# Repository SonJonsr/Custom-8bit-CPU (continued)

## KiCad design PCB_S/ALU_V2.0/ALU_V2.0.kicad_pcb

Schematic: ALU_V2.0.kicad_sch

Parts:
C1, C2, C3, C4, C5, C6, C7, C8: 22uF; C_0805; Voltage Rated 25V; Tolerance ±20%; Part CL21A226MAQNNNE; LCSC C45783
D1, D2, D3, D4, D5, D6, D7, D8, D9, D10, D11, D12, D13, D14, D15, D16, D17, D18, D19, D20, D21, D22, D23, D24, D25, D26, D27, D28, D29, D30, D31, D32, D33, D34, D35, D36: Red; D_0603; Part KT-0603R; LCSC C2286
H1, H2, H3, H4: MountingHole; MountingHole_3.2mm_M3
J1, J2, J3: Conn_02x08_Odd_Even; PinSocket_2x08_P2.54mm_Vertical
J4, J6: Conn_01x02_Pin; PinHeader_1x02_P2.54mm_Vertical
Q1, Q2, Q3, Q4, Q5, Q6, Q7, Q8, Q9, Q10, Q11, Q12, Q13, Q14, Q15, Q16, Q17, Q18, Q19, Q20, Q21, Q22, Q23, Q24, Q25, Q26, Q27, Q28, Q29, Q30, Q31, Q32, Q33, Q34, Q35, Q36, Q37, Q38, Q39, Q40, Q41, Q42, Q43, Q44, Q45, Q46, Q47, Q48, Q49, Q50, Q51, Q52, Q53, Q54, Q55, Q56, Q57, Q58, Q59, Q60, Q61, Q62, Q63, Q64, Q65, Q66, Q67, Q68, Q69, Q70, Q71, Q72, Q73, Q74, Q75, Q76, Q77, Q78, Q79, Q80, Q81, Q82, Q83, Q84, Q85, Q86, Q87, Q88, Q89, Q90, Q91, Q92, Q93, Q94, Q95, Q96, Q97, Q98, Q99, Q100, Q101, Q102, Q103, Q104, Q105, Q106, Q107, Q108, Q109, Q110, Q111, Q112, Q113, Q114, Q115, Q116, Q117, Q118, Q119, Q120, Q121, Q122, Q123, Q124, Q125, Q126, Q127, Q128, Q129, Q130, Q131, Q132, Q133, Q134, Q135, Q136, Q137, Q138, Q139, Q140, Q141, Q142, Q143, Q144, Q145, Q146, Q147, Q148, Q149, Q150, Q151, Q152, Q153, Q154, Q155, Q156, Q157, Q158, Q159, Q160, Q161, Q162, Q163, Q164, Q165, Q166, Q167, Q168, Q169, Q170, Q171, Q172, Q173, Q174, Q175, Q176, Q177, Q178, Q179, Q180, Q181, Q182, Q183, Q184, Q185, Q186, Q187, Q188, Q189, Q190, Q191, Q192, Q193, Q194, Q195, Q196, Q197, Q198, Q199, Q200, Q201, Q202, Q203, Q204, Q205, Q206, Q207, Q208, Q209, Q210, Q211, Q212, Q213, Q214, Q215, Q216, Q217, Q218, Q219, Q220, Q221, Q222, Q223, Q224, Q225, Q226, Q227, Q228, Q229, Q230, Q231, Q232, Q233, Q234, Q235, Q236, Q237, Q238, Q239, Q240, Q241, Q242, Q243, Q244, Q245, Q246, Q247, Q248, Q249, Q250, Q251, Q252, Q253, Q254, Q255, Q256, Q257, Q258, Q259, Q260, Q261, Q262, Q263, Q264, Q265, Q266, Q267, Q268, Q269, Q270, Q271, Q277, Q278, Q279, Q280, Q281, Q282, Q283, Q284, Q285, Q286, Q287, Q288, Q289, Q290: 2N7002; SOT-23; Part 2N7002; LCSC C8545
Q272, Q273, Q274, Q275, Q276, Q291, Q292, Q293, Q294, Q295, Q296, Q297, Q298, Q299, Q300, Q301, Q302, Q303, Q304, Q305, Q306, Q307, Q308, Q309, Q310, Q311, Q312, Q313, Q314, Q315, Q316, Q317, Q318, Q319, Q320: 2N7002; SOT-23
R1, R2, R3, R4, R5, R6, R7, R8, R9, R10, R11, R12, R13, R14, R15, R16, R17, R18, R19, R20, R21, R22, R23, R24, R25, R26, R27, R28, R29, R30, R31, R32, R33, R34, R35, R36, R37, R38, R39, R40, R41, R42, R43, R44, R45, R46, R47, R48, R49, R50, R51, R52, R53, R54, R55, R56, R57, R58, R59, R60, R61, R62, R63, R64, R65, R66, R67, R68, R69, R70, R71, R72, R73, R74, R75, R76, R77, R78, R79, R80, R81, R82, R83, R84, R85, R86, R87, R88, R89, R90, R91, R92, R93, R94, R95, R96, R97, R98, R99, R100, R101, R102, R103, R104, R105, R106, R107, R108, R109, R110, R111, R112, R113, R114, R115, R116, R117, R118, R119, R120, R121, R122, R123, R124, R125, R126, R127, R128, R129, R130, R131, R132, R133, R134, R135, R136, R137, R138, R139, R140, R141, R142, R143, R144, R145, R146, R147, R148, R149, R150, R151, R152, R153, R154, R155, R156, R157, R158, R159, R160, R161, R162, R163, R164, R165, R166, R167, R168, R169, R170, R171, R172, R173, R174, R175, R176, R177, R178, R179, R180, R181, R182, R183, R184, R185, R186, R187, R188, R189, R190, R191, R192, R193, R194, R195, R196, R197, R198, R199, R200, R201, R202, R203, R204: 10kΩ; R_0402; Overload Voltage (Max) 50V; Tolerance ±1%; Part 0402WGF1002TCE; LCSC C25744

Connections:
/C_in: J2.14, Q28.1 (G)
/C_out: J2.12, Q265.3 (D), Q320.1 (G), R125.2
/N: J1.15, J2.4, Q253.3 (D), Q279.1 (G), Q282.1 (G), Q290.1 (G), Q293.1 (G), Q310.1 (G), R120.2
/O: J2.10, Q286.3 (D), Q319.1 (G), R133.2
/U: J2.8, Q264.3 (D), Q318.1 (G), R124.2
/Z: J2.6, Q268.3 (D), Q269.3 (D), Q270.3 (D), Q271.3 (D), Q287.3 (D), Q288.3 (D), Q289.3 (D), Q290.3 (D), Q311.1 (G), R127.2
GND: C1.2, C2.2, C3.2, C4.2, C5.2, C6.2, C7.2, C8.2, D36.1, J1.4, J1.8, J1.12, J1.16, J2.2, J2.16, J4.2, J6.2, Q1.2 (S), Q2.2 (S), Q3.2 (S), Q4.2 (S), Q5.2 (S), Q6.2 (S), Q7.2 (S), Q8.2 (S), Q9.2 (S), Q10.2 (S), Q11.2 (S), Q12.2 (S), Q13.2 (S), Q14.2 (S), Q15.2 (S), Q16.2 (S), Q17.2 (S), Q18.2 (S), Q19.2 (S), Q20.2 (S), Q21.2 (S), Q22.2 (S), Q23.2 (S), Q24.2 (S), Q26.2 (S), Q28.2 (S), Q31.2 (S), Q33.2 (S), Q35.2 (S), Q38.2 (S), Q41.2 (S), Q43.2 (S), Q46.2 (S), Q48.2 (S), Q50.2 (S), Q53.2 (S), Q56.2 (S), Q58.2 (S), Q61.2 (S), Q63.2 (S), Q65.2 (S), Q68.2 (S), Q71.2 (S), Q73.2 (S), Q76.2 (S), Q78.2 (S), Q80.2 (S), Q83.2 (S), Q86.2 (S), Q88.2 (S), Q91.2 (S), Q93.2 (S), Q95.2 (S), Q98.2 (S), Q101.2 (S), Q103.2 (S), Q106.2 (S), Q108.2 (S), Q110.2 (S), Q113.2 (S), Q116.2 (S), Q118.2 (S), Q121.2 (S), Q123.2 (S), Q125.2 (S), Q128.2 (S), Q131.2 (S), Q133.2 (S), Q136.2 (S), Q138.2 (S), Q140.2 (S), Q143.2 (S), Q146.2 (S), Q155.2 (S), Q156.2 (S), Q157.2 (S), Q158.2 (S), Q159.2 (S), Q160.2 (S), Q161.2 (S), Q162.2 (S), Q164.2 (S), Q166.2 (S), Q168.2 (S), Q170.2 (S), Q172.2 (S), Q174.2 (S), Q176.2 (S), Q178.2 (S), Q180.2 (S), Q182.2 (S), Q184.2 (S), Q186.2 (S), Q188.2 (S), Q190.2 (S), Q192.2 (S), Q194.2 (S), Q196.2 (S), Q198.2 (S), Q200.2 (S), Q202.2 (S), Q204.2 (S), Q206.2 (S), Q208.2 (S), Q210.2 (S), Q212.2 (S), Q214.2 (S), Q216.2 (S), Q218.2 (S), Q220.2 (S), Q222.2 (S), Q224.2 (S), Q226.2 (S), Q228.2 (S), Q230.2 (S), Q232.2 (S), Q234.2 (S), Q236.2 (S), Q238.2 (S), Q240.2 (S), Q242.2 (S), Q244.2 (S), Q246.2 (S), Q248.2 (S), Q250.2 (S), Q252.2 (S), Q254.2 (S), Q255.2 (S), Q256.2 (S), Q257.2 (S), Q258.2 (S), Q259.2 (S), Q260.2 (S), Q261.2 (S), Q263.2 (S), Q264.2 (S), Q265.2 (S), Q267.2 (S), Q268.2 (S), Q269.2 (S), Q270.2 (S), Q271.2 (S), Q272.2 (S), Q273.2 (S), Q274.2 (S), Q275.2 (S), Q276.2 (S), Q277.2 (S), Q278.2 (S), Q281.2 (S), Q282.2 (S), Q285.2 (S), Q286.2 (S), Q287.2 (S), Q288.2 (S), Q289.2 (S), Q290.2 (S), Q291.2 (S), Q292.2 (S), Q293.2 (S), Q294.2 (S), Q295.2 (S), Q296.2 (S), Q297.2 (S), Q298.2 (S), Q299.2 (S), Q300.2 (S), Q301.2 (S), Q302.2 (S), Q303.2 (S), Q304.2 (S), Q305.2 (S), Q306.2 (S), Q307.2 (S), Q308.2 (S), Q309.2 (S), Q310.2 (S), Q311.2 (S), Q312.2 (S), Q313.2 (S), Q314.2 (S), Q315.2 (S), Q316.2 (S), Q317.2 (S), Q318.2 (S), Q319.2 (S), Q320.2 (S)
unnamed: D1.2, R128.2, R134.2
unnamed: D2.2, R135.2, R136.2
unnamed: D3.2, R137.2, R138.2
unnamed: D4.2, R139.2, R140.2
unnamed: D5.2, R175.2, R176.2
unnamed: D6.2, R177.2, R178.2
unnamed: D7.2, R179.2, R180.2
unnamed: D8.2, R181.2, R182.2
unnamed: D9.2, R141.2, R142.2
unnamed: D10.2, R143.2, R144.2
unnamed: D11.2, R145.2, R146.2
unnamed: D12.2, R147.2, R148.2
unnamed: D13.2, R189.2, R190.2
unnamed: D14.2, R191.2, R192.2
unnamed: D15.2, R193.2, R194.2
unnamed: D16.2, R195.2, R196.2
unnamed: D17.2, R149.2, R150.2
unnamed: D18.2, R151.2, R152.2
unnamed: D19.2, R153.2, R154.2
unnamed: D20.2, R155.2, R156.2
unnamed: D21.2, R197.2, R198.2
unnamed: D22.2, R199.2, R200.2
unnamed: D23.2, R201.2, R202.2
unnamed: D24.2, R203.2, R204.2
unnamed: D25.2, R173.2, R174.2
unnamed: D26.2, R171.2, R172.2
unnamed: D27.2, R159.2, R160.2
unnamed: D28.2, R161.2, R162.2
unnamed: D29.2, R163.2, R164.2
unnamed: D30.2, R183.2, R184.2
unnamed: D31.2, R185.2, R186.2
unnamed: D32.2, R187.2, R188.2
unnamed: D33.2, R167.2, R170.2
unnamed: D34.2, R165.2, R166.2
unnamed: D35.2, R157.2, R158.2
unnamed: D36.2, R168.2, R169.2
unnamed: J1.1, Q239.3 (D), Q268.1 (G), Q273.1 (G), R113.2
unnamed: J1.3, Q241.3 (D), Q269.1 (G), Q272.1 (G), R114.2
unnamed: J1.5, Q243.3 (D), Q270.1 (G), Q274.1 (G), R115.2
unnamed: J1.7, Q245.3 (D), Q271.1 (G), Q275.1 (G), R116.2
unnamed: J1.9, Q247.3 (D), Q276.1 (G), Q287.1 (G), R117.2
unnamed: J1.11, Q249.3 (D), Q288.1 (G), Q291.1 (G), R118.2
unnamed: J1.13, Q251.3 (D), Q289.1 (G), Q292.1 (G), R119.2
unnamed: J2.3, Q210.1 (G), Q212.1 (G), Q214.1 (G), Q216.1 (G), Q218.1 (G), Q220.1 (G), Q222.1 (G), Q224.1 (G), Q260.1 (G), Q267.1 (G), Q317.1 (G)
unnamed: J2.5, Q180.1 (G), Q184.1 (G), Q188.1 (G), Q192.1 (G), Q196.1 (G), Q200.1 (G), Q204.1 (G), Q208.1 (G), Q259.1 (G), Q316.1 (G)
unnamed: J2.7, Q178.1 (G), Q182.1 (G), Q186.1 (G), Q190.1 (G), Q194.1 (G), Q198.1 (G), Q202.1 (G), Q206.1 (G), Q258.1 (G), Q315.1 (G)
unnamed: J2.9, Q226.1 (G), Q228.1 (G), Q230.1 (G), Q232.1 (G), Q234.1 (G), Q236.1 (G), Q238.1 (G), Q257.1 (G), Q263.1 (G), Q314.1 (G)
unnamed: J2.11, Q146.1 (G), Q164.1 (G), Q166.1 (G), Q168.1 (G), Q170.1 (G), Q172.1 (G), Q174.1 (G), Q176.1 (G), Q256.1 (G), Q313.1 (G)
unnamed: J2.13, Q155.1 (G), Q156.1 (G), Q157.1 (G), Q158.1 (G), Q159.1 (G), Q160.1 (G), Q161.1 (G), Q162.1 (G), Q255.1 (G), Q312.1 (G)
unnamed: J3.1, Q2.1 (G), Q34.1 (G), Q36.1 (G), Q294.1 (G)
unnamed: J3.2, Q1.1 (G), Q33.1 (G), Q262.1 (G), Q302.1 (G)
unnamed: J3.3, Q5.1 (G), Q49.1 (G), Q51.1 (G), Q295.1 (G)
unnamed: J3.4, Q4.1 (G), Q48.1 (G), Q225.1 (G), Q303.1 (G)
unnamed: J3.5, Q8.1 (G), Q64.1 (G), Q66.1 (G), Q296.1 (G)
unnamed: J3.6, Q7.1 (G), Q63.1 (G), Q227.1 (G), Q304.1 (G)
unnamed: J3.7, Q11.1 (G), Q79.1 (G), Q81.1 (G), Q297.1 (G)
unnamed: J3.8, Q10.1 (G), Q78.1 (G), Q229.1 (G), Q305.1 (G)
unnamed: J3.9, Q14.1 (G), Q94.1 (G), Q96.1 (G), Q298.1 (G)
unnamed: J3.10, Q13.1 (G), Q93.1 (G), Q231.1 (G), Q306.1 (G)
unnamed: J3.11, Q17.1 (G), Q109.1 (G), Q111.1 (G), Q299.1 (G)
unnamed: J3.12, Q16.1 (G), Q108.1 (G), Q233.1 (G), Q307.1 (G)
unnamed: J3.13, Q20.1 (G), Q124.1 (G), Q126.1 (G), Q300.1 (G)
unnamed: J3.14, Q19.1 (G), Q123.1 (G), Q235.1 (G), Q308.1 (G)
unnamed: J3.15, Q23.1 (G), Q139.1 (G), Q141.1 (G), Q278.1 (G), Q284.1 (G), Q301.1 (G)
unnamed: J3.16, Q22.1 (G), Q138.1 (G), Q237.1 (G), Q277.1 (G), Q285.1 (G), Q309.1 (G)
unnamed: Q1.3 (D), Q2.3 (D), Q3.1 (G), R1.2
unnamed: Q4.3 (D), Q5.3 (D), Q6.1 (G), R3.2
unnamed: Q7.3 (D), Q8.3 (D), Q9.1 (G), R5.2
unnamed: Q10.3 (D), Q11.3 (D), Q12.1 (G), R7.2
unnamed: Q12.3 (D), Q151.1 (G), R8.2
unnamed: Q13.3 (D), Q14.3 (D), Q15.1 (G), R9.2
unnamed: Q15.3 (D), Q150.1 (G), R10.2
unnamed: Q16.3 (D), Q17.3 (D), Q18.1 (G), R11.2
unnamed: Q19.3 (D), Q20.3 (D), Q21.1 (G), R13.2
unnamed: Q22.3 (D), Q23.3 (D), Q24.1 (G), R15.2
unnamed: Q25.3 (D), Q26.1 (G), R17.2
unnamed: Q25.1 (G), Q30.1 (G), Q34.3 (D), Q35.1 (G), R23.2
unnamed: Q26.3 (D), Q27.2 (S)
unnamed: Q27.1 (G), Q36.3 (D), R25.2
unnamed: Q28.3 (D), Q29.2 (S), Q37.2 (S)
unnamed: Q29.3 (D), Q31.1 (G), R19.2
unnamed: Q29.1 (G), Q37.3 (D), Q38.1 (G), R26.2
unnamed: Q30.3 (D), Q43.1 (G), R20.2
unnamed: Q30.2 (S), Q38.3 (D), Q39.2 (S)
unnamed: Q31.3 (D), Q32.2 (S)
unnamed: Q32.1 (G), Q39.3 (D), R27.2
unnamed: Q40.3 (D), Q41.1 (G), R28.2
unnamed: Q40.1 (G), Q45.1 (G), Q49.3 (D), Q50.1 (G), R34.2
unnamed: Q41.3 (D), Q42.2 (S)
unnamed: Q42.1 (G), Q51.3 (D), R36.2
unnamed: Q43.3 (D), Q44.2 (S), Q52.2 (S)
unnamed: Q44.3 (D), Q46.1 (G), R30.2
unnamed: Q44.1 (G), Q52.3 (D), Q53.1 (G), R37.2
unnamed: Q45.3 (D), Q58.1 (G), R31.2
unnamed: Q45.2 (S), Q53.3 (D), Q54.2 (S)
unnamed: Q46.3 (D), Q47.2 (S)
unnamed: Q47.1 (G), Q54.3 (D), R38.2
unnamed: Q55.3 (D), Q56.1 (G), R39.2
unnamed: Q55.1 (G), Q60.1 (G), Q64.3 (D), Q65.1 (G), R45.2
unnamed: Q56.3 (D), Q57.2 (S)
unnamed: Q57.1 (G), Q66.3 (D), R47.2
unnamed: Q58.3 (D), Q59.2 (S), Q67.2 (S)
unnamed: Q59.3 (D), Q61.1 (G), R41.2
unnamed: Q59.1 (G), Q67.3 (D), Q68.1 (G), R48.2
unnamed: Q60.3 (D), Q73.1 (G), R42.2
unnamed: Q60.2 (S), Q68.3 (D), Q69.2 (S)
unnamed: Q61.3 (D), Q62.2 (S)
unnamed: Q62.1 (G), Q69.3 (D), R49.2
unnamed: Q70.3 (D), Q71.1 (G), R50.2
unnamed: Q70.1 (G), Q75.1 (G), Q79.3 (D), Q80.1 (G), R56.2
unnamed: Q71.3 (D), Q72.2 (S)
unnamed: Q72.1 (G), Q81.3 (D), R58.2
unnamed: Q73.3 (D), Q74.2 (S), Q82.2 (S)
unnamed: Q74.3 (D), Q76.1 (G), R52.2
unnamed: Q74.1 (G), Q82.3 (D), Q83.1 (G), R59.2
unnamed: Q75.3 (D), Q88.1 (G), R53.2
unnamed: Q75.2 (S), Q83.3 (D), Q84.2 (S)
unnamed: Q76.3 (D), Q77.2 (S)
unnamed: Q77.1 (G), Q84.3 (D), R60.2
unnamed: Q85.3 (D), Q86.1 (G), R61.2
unnamed: Q85.1 (G), Q90.1 (G), Q94.3 (D), Q95.1 (G), R67.2
unnamed: Q86.3 (D), Q87.2 (S)
unnamed: Q87.1 (G), Q96.3 (D), R69.2
unnamed: Q88.3 (D), Q89.2 (S), Q97.2 (S)
unnamed: Q89.3 (D), Q91.1 (G), R63.2
unnamed: Q89.1 (G), Q97.3 (D), Q98.1 (G), R70.2
unnamed: Q90.2 (S), Q98.3 (D), Q99.2 (S)
unnamed: Q91.3 (D), Q92.2 (S)
unnamed: Q92.1 (G), Q99.3 (D), R71.2
unnamed: Q100.3 (D), Q101.1 (G), R72.2
unnamed: Q100.1 (G), Q105.1 (G), Q109.3 (D), Q110.1 (G), R78.2
unnamed: Q100.2 (S), Q108.3 (D), Q109.2 (S), Q197.1 (G), R77.2
unnamed: Q101.3 (D), Q102.2 (S)
unnamed: Q102.3 (D), Q112.1 (G), Q114.1 (G), Q199.1 (G), R73.2
unnamed: Q102.1 (G), Q111.3 (D), R80.2
unnamed: Q103.3 (D), Q104.2 (S), Q112.2 (S)
unnamed: Q90.3 (D), Q103.1 (G), R64.2
unnamed: Q104.3 (D), Q106.1 (G), R74.2
unnamed: Q104.1 (G), Q112.3 (D), Q113.1 (G), R81.2
unnamed: Q105.3 (D), Q118.1 (G), R75.2
unnamed: Q105.2 (S), Q113.3 (D), Q114.2 (S)
unnamed: Q106.3 (D), Q107.2 (S)
unnamed: Q107.3 (D), Q219.1 (G), R76.2
unnamed: Q107.1 (G), Q114.3 (D), R82.2
unnamed: Q110.3 (D), Q111.2 (S), Q171.1 (G), R79.2
unnamed: Q115.3 (D), Q116.1 (G), R83.2
unnamed: Q115.1 (G), Q120.1 (G), Q124.3 (D), Q125.1 (G), R89.2
unnamed: Q115.2 (S), Q123.3 (D), Q124.2 (S), Q201.1 (G), R88.2
unnamed: Q116.3 (D), Q117.2 (S)
unnamed: Q117.3 (D), Q127.1 (G), Q129.1 (G), Q203.1 (G), R84.2
unnamed: Q117.1 (G), Q126.3 (D), R91.2
unnamed: Q118.3 (D), Q119.2 (S), Q127.2 (S)
unnamed: Q119.3 (D), Q121.1 (G), R85.2
unnamed: Q119.1 (G), Q127.3 (D), Q128.1 (G), R92.2
unnamed: Q120.3 (D), Q133.1 (G), R86.2
unnamed: Q120.2 (S), Q128.3 (D), Q129.2 (S)
unnamed: Q121.3 (D), Q122.2 (S)
unnamed: Q122.3 (D), Q221.1 (G), R87.2
unnamed: Q122.1 (G), Q129.3 (D), R93.2
unnamed: Q125.3 (D), Q126.2 (S), Q173.1 (G), R90.2
unnamed: Q130.3 (D), Q131.1 (G), R94.2
unnamed: Q130.1 (G), Q135.1 (G), Q139.3 (D), Q140.1 (G), R100.2
unnamed: Q130.2 (S), Q138.3 (D), Q139.2 (S), Q205.1 (G), R99.2
unnamed: Q131.3 (D), Q132.2 (S)
unnamed: Q132.3 (D), Q142.1 (G), Q144.1 (G), Q207.1 (G), R95.2
unnamed: Q132.1 (G), Q141.3 (D), R102.2
unnamed: Q133.3 (D), Q134.2 (S), Q142.2 (S)
unnamed: Q134.3 (D), Q136.1 (G), R96.2
unnamed: Q134.1 (G), Q142.3 (D), Q143.1 (G), R103.2
unnamed: Q135.3 (D), Q266.1 (G), R97.2
unnamed: Q135.2 (S), Q143.3 (D), Q144.2 (S)
unnamed: Q136.3 (D), Q137.2 (S)
unnamed: Q137.3 (D), Q223.1 (G), R98.2
unnamed: Q137.1 (G), Q144.3 (D), R104.2
unnamed: Q140.3 (D), Q141.2 (S), Q175.1 (G), R101.2
unnamed: Q145.3 (D), Q154.3 (D), Q177.3 (D), Q179.3 (D), Q209.3 (D), Q225.3 (D), Q239.1 (G), R105.2
unnamed: Q35.3 (D), Q36.2 (S), Q145.1 (G), R24.2
unnamed: Q145.2 (S), Q146.3 (D)
unnamed: Q147.3 (D), Q175.3 (D), Q205.3 (D), Q207.3 (D), Q223.3 (D), Q253.1 (G), R112.2
unnamed: Q24.3 (D), Q147.1 (G), R16.2
unnamed: Q147.2 (S), Q162.3 (D)
unnamed: Q148.3 (D), Q173.3 (D), Q201.3 (D), Q203.3 (D), Q221.3 (D), Q237.3 (D), Q251.1 (G), R111.2
unnamed: Q21.3 (D), Q148.1 (G), R14.2
unnamed: Q148.2 (S), Q161.3 (D)
unnamed: Q149.3 (D), Q171.3 (D), Q197.3 (D), Q199.3 (D), Q219.3 (D), Q235.3 (D), Q249.1 (G), R110.2
unnamed: Q18.3 (D), Q149.1 (G), R12.2
unnamed: Q149.2 (S), Q160.3 (D)
unnamed: Q150.3 (D), Q169.3 (D), Q193.3 (D), Q195.3 (D), Q217.3 (D), Q233.3 (D), Q247.1 (G), R109.2
unnamed: Q150.2 (S), Q159.3 (D)
unnamed: Q151.3 (D), Q167.3 (D), Q189.3 (D), Q191.3 (D), Q215.3 (D), Q231.3 (D), Q245.1 (G), R108.2
unnamed: Q151.2 (S), Q158.3 (D)
unnamed: Q152.3 (D), Q165.3 (D), Q185.3 (D), Q187.3 (D), Q213.3 (D), Q229.3 (D), Q243.1 (G), R107.2
unnamed: Q9.3 (D), Q152.1 (G), R6.2
unnamed: Q152.2 (S), Q157.3 (D)
unnamed: Q153.3 (D), Q163.3 (D), Q181.3 (D), Q183.3 (D), Q211.3 (D), Q227.3 (D), Q241.1 (G), R106.2
unnamed: Q6.3 (D), Q153.1 (G), R4.2
unnamed: Q153.2 (S), Q156.3 (D)
unnamed: Q3.3 (D), Q154.1 (G), R2.2
unnamed: Q154.2 (S), Q155.3 (D)
unnamed: Q50.3 (D), Q51.2 (S), Q163.1 (G), R35.2
unnamed: Q163.2 (S), Q164.3 (D)
unnamed: Q65.3 (D), Q66.2 (S), Q165.1 (G), R46.2
unnamed: Q165.2 (S), Q166.3 (D)
unnamed: Q80.3 (D), Q81.2 (S), Q167.1 (G), R57.2
unnamed: Q167.2 (S), Q168.3 (D)
unnamed: Q95.3 (D), Q96.2 (S), Q169.1 (G), R68.2
unnamed: Q169.2 (S), Q170.3 (D)
unnamed: Q171.2 (S), Q172.3 (D)
unnamed: Q173.2 (S), Q174.3 (D)
unnamed: Q175.2 (S), Q176.3 (D)
unnamed: Q25.2 (S), Q33.3 (D), Q34.2 (S), Q177.1 (G), R22.2
unnamed: Q177.2 (S), Q178.3 (D)
unnamed: Q27.3 (D), Q37.1 (G), Q39.1 (G), Q179.1 (G), R18.2
unnamed: Q179.2 (S), Q180.3 (D)
unnamed: Q40.2 (S), Q48.3 (D), Q49.2 (S), Q181.1 (G), R33.2
unnamed: Q181.2 (S), Q182.3 (D)
unnamed: Q42.3 (D), Q52.1 (G), Q54.1 (G), Q183.1 (G), R29.2
unnamed: Q183.2 (S), Q184.3 (D)
unnamed: Q55.2 (S), Q63.3 (D), Q64.2 (S), Q185.1 (G), R44.2
unnamed: Q185.2 (S), Q186.3 (D)
unnamed: Q57.3 (D), Q67.1 (G), Q69.1 (G), Q187.1 (G), R40.2
unnamed: Q187.2 (S), Q188.3 (D)
unnamed: Q70.2 (S), Q78.3 (D), Q79.2 (S), Q189.1 (G), R55.2
unnamed: Q189.2 (S), Q190.3 (D)
unnamed: Q72.3 (D), Q82.1 (G), Q84.1 (G), Q191.1 (G), R51.2
unnamed: Q191.2 (S), Q192.3 (D)
unnamed: Q85.2 (S), Q93.3 (D), Q94.2 (S), Q193.1 (G), R66.2
unnamed: Q193.2 (S), Q194.3 (D)
unnamed: Q87.3 (D), Q97.1 (G), Q99.1 (G), Q195.1 (G), R62.2
unnamed: Q195.2 (S), Q196.3 (D)
unnamed: Q197.2 (S), Q198.3 (D)
unnamed: Q199.2 (S), Q200.3 (D)
unnamed: Q201.2 (S), Q202.3 (D)
unnamed: Q203.2 (S), Q204.3 (D)
unnamed: Q205.2 (S), Q206.3 (D)
unnamed: Q207.2 (S), Q208.3 (D)
unnamed: Q32.3 (D), Q209.1 (G), R21.2
unnamed: Q209.2 (S), Q210.3 (D)
unnamed: Q47.3 (D), Q211.1 (G), R32.2
unnamed: Q211.2 (S), Q212.3 (D)
unnamed: Q62.3 (D), Q213.1 (G), R43.2
unnamed: Q213.2 (S), Q214.3 (D)
unnamed: Q77.3 (D), Q215.1 (G), R54.2
unnamed: Q215.2 (S), Q216.3 (D)
unnamed: Q92.3 (D), Q217.1 (G), R65.2
unnamed: Q217.2 (S), Q218.3 (D)
unnamed: Q219.2 (S), Q220.3 (D)
unnamed: Q221.2 (S), Q222.3 (D)
unnamed: Q223.2 (S), Q224.3 (D)
unnamed: Q225.2 (S), Q226.3 (D)
unnamed: Q227.2 (S), Q228.3 (D)
unnamed: Q229.2 (S), Q230.3 (D)
unnamed: Q231.2 (S), Q232.3 (D)
unnamed: Q233.2 (S), Q234.3 (D)
unnamed: Q235.2 (S), Q236.3 (D)
unnamed: Q237.2 (S), Q238.3 (D)
unnamed: Q239.2 (S), Q240.3 (D)
unnamed: Q240.1 (G), Q242.1 (G), Q244.1 (G), Q246.1 (G), Q248.1 (G), Q250.1 (G), Q252.1 (G), Q254.1 (G), Q261.3 (D), R121.2
unnamed: Q241.2 (S), Q242.3 (D)
unnamed: Q243.2 (S), Q244.3 (D)
unnamed: Q245.2 (S), Q246.3 (D)
unnamed: Q247.2 (S), Q248.3 (D)
unnamed: Q249.2 (S), Q250.3 (D)
unnamed: Q251.2 (S), Q252.3 (D)
unnamed: Q253.2 (S), Q254.3 (D)
unnamed: Q255.3 (D), Q256.3 (D), Q257.3 (D), Q258.3 (D), Q259.3 (D), Q260.3 (D), Q261.1 (G), R122.2
unnamed: Q262.3 (D), Q264.1 (G), R123.2
unnamed: Q262.2 (S), Q263.3 (D)
unnamed: Q265.1 (G), Q266.3 (D), R126.2
unnamed: Q266.2 (S), Q267.3 (D)
unnamed: D2.1, Q272.3 (D)
unnamed: D1.1, Q273.3 (D)
unnamed: D3.1, Q274.3 (D)
unnamed: D4.1, Q275.3 (D)
unnamed: D5.1, Q276.3 (D)
unnamed: Q277.3 (D), Q281.1 (G), R129.2
unnamed: Q278.3 (D), Q280.1 (G), R130.2
unnamed: Q279.3 (D), Q283.3 (D), Q286.1 (G), R132.2
unnamed: Q279.2 (S), Q280.3 (D)
unnamed: Q280.2 (S), Q281.3 (D)
unnamed: Q282.3 (D), Q283.1 (G), R131.2
unnamed: Q283.2 (S), Q284.3 (D)
unnamed: Q284.2 (S), Q285.3 (D)
unnamed: D6.1, Q291.3 (D)
unnamed: D7.1, Q292.3 (D)
unnamed: D8.1, Q293.3 (D)
unnamed: D9.1, Q294.3 (D)
unnamed: D10.1, Q295.3 (D)
unnamed: D11.1, Q296.3 (D)
unnamed: D12.1, Q297.3 (D)
unnamed: D13.1, Q298.3 (D)
unnamed: D14.1, Q299.3 (D)
unnamed: D15.1, Q300.3 (D)
unnamed: D16.1, Q301.3 (D)
unnamed: D17.1, Q302.3 (D)
unnamed: D18.1, Q303.3 (D)
unnamed: D19.1, Q304.3 (D)
unnamed: D20.1, Q305.3 (D)
unnamed: D21.1, Q306.3 (D)
unnamed: D22.1, Q307.3 (D)
unnamed: D23.1, Q308.3 (D)
unnamed: D24.1, Q309.3 (D)
unnamed: D25.1, Q310.3 (D)
unnamed: D26.1, Q311.3 (D)
unnamed: D27.1, Q312.3 (D)
unnamed: D28.1, Q313.3 (D)
unnamed: D29.1, Q314.3 (D)
unnamed: D30.1, Q315.3 (D)
unnamed: D31.1, Q316.3 (D)
unnamed: D32.1, Q317.3 (D)
unnamed: D33.1, Q318.3 (D)
unnamed: D34.1, Q319.3 (D)
unnamed: D35.1, Q320.3 (D)
VCC: C1.1, C2.1, C3.1, C4.1, C5.1, C6.1, C7.1, C8.1, J1.2, J1.6, J1.10, J1.14, J2.1, J2.15, J4.1, J6.1, R1.1, R2.1, R3.1, R4.1, R5.1, R6.1, R7.1, R8.1, R9.1, R10.1, R11.1, R12.1, R13.1, R14.1, R15.1, R16.1, R17.1, R18.1, R19.1, R20.1, R21.1, R22.1, R23.1, R24.1, R25.1, R26.1, R27.1, R28.1, R29.1, R30.1, R31.1, R32.1, R33.1, R34.1, R35.1, R36.1, R37.1, R38.1, R39.1, R40.1, R41.1, R42.1, R43.1, R44.1, R45.1, R46.1, R47.1, R48.1, R49.1, R50.1, R51.1, R52.1, R53.1, R54.1, R55.1, R56.1, R57.1, R58.1, R59.1, R60.1, R61.1, R62.1, R63.1, R64.1, R65.1, R66.1, R67.1, R68.1, R69.1, R70.1, R71.1, R72.1, R73.1, R74.1, R75.1, R76.1, R77.1, R78.1, R79.1, R80.1, R81.1, R82.1, R83.1, R84.1, R85.1, R86.1, R87.1, R88.1, R89.1, R90.1, R91.1, R92.1, R93.1, R94.1, R95.1, R96.1, R97.1, R98.1, R99.1, R100.1, R101.1, R102.1, R103.1, R104.1, R105.1, R106.1, R107.1, R108.1, R109.1, R110.1, R111.1, R112.1, R113.1, R114.1, R115.1, R116.1, R117.1, R118.1, R119.1, R120.1, R121.1, R122.1, R123.1, R124.1, R125.1, R126.1, R127.1, R128.1, R129.1, R130.1, R131.1, R132.1, R133.1, R134.1, R135.1, R136.1, R137.1, R138.1, R139.1, R140.1, R141.1, R142.1, R143.1, R144.1, R145.1, R146.1, R147.1, R148.1, R149.1, R150.1, R151.1, R152.1, R153.1, R154.1, R155.1, R156.1, R157.1, R158.1, R159.1, R160.1, R161.1, R162.1, R163.1, R164.1, R165.1, R166.1, R167.1, R168.1, R169.1, R170.1, R171.1, R172.1, R173.1, R174.1, R175.1, R176.1, R177.1, R178.1, R179.1, R180.1, R181.1, R182.1, R183.1, R184.1, R185.1, R186.1, R187.1, R188.1, R189.1, R190.1, R191.1, R192.1, R193.1, R194.1, R195.1, R196.1, R197.1, R198.1, R199.1, R200.1, R201.1, R202.1, R203.1, R204.1

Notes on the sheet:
Result
Dont need these resistors
Carry Inn
Pin 1 is Most Significant Bit
ADD
NOT
AND
XOR

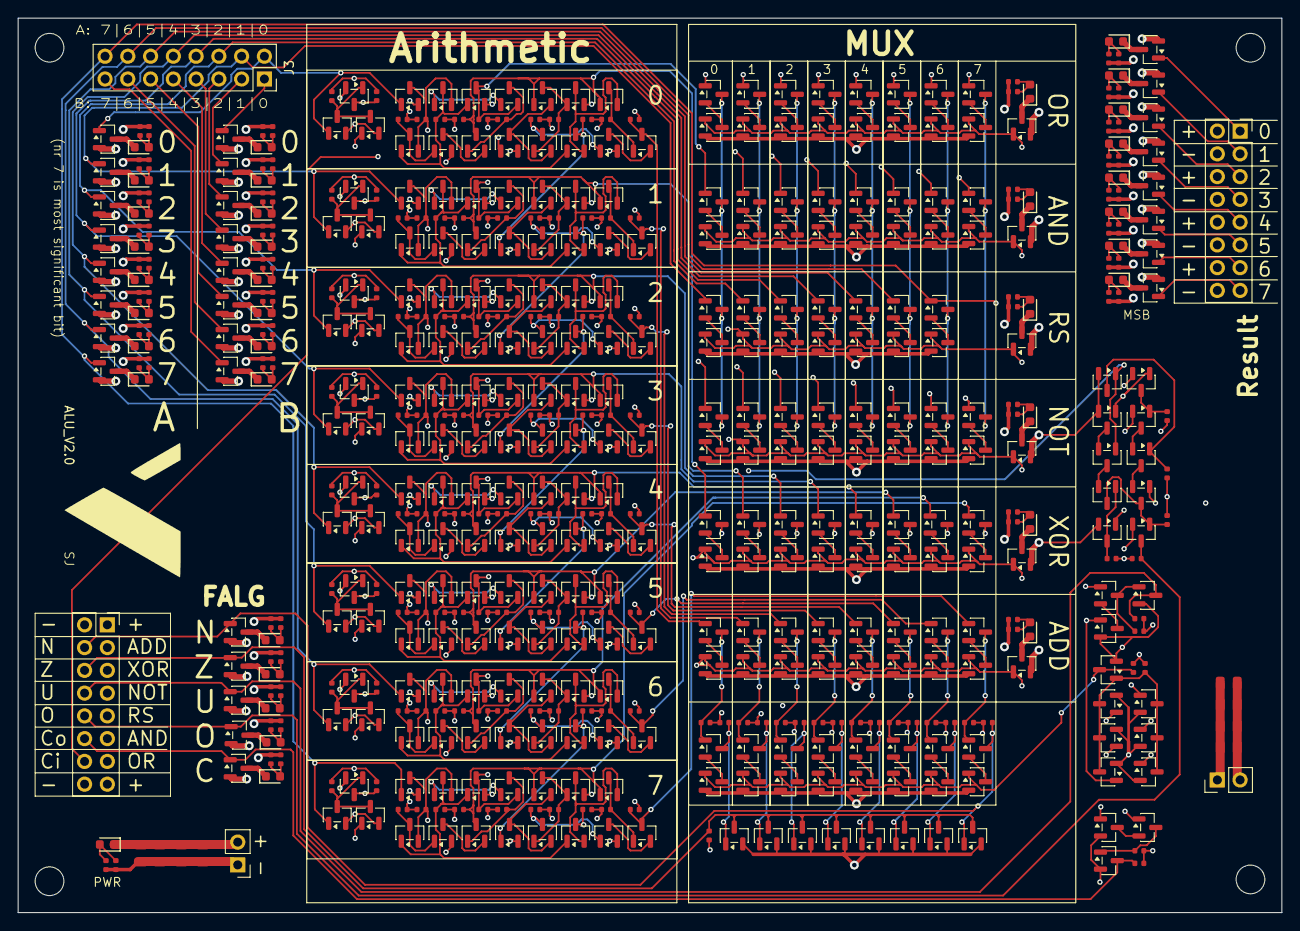
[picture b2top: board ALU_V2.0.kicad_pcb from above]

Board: 6 copper layers, 141.0 x 99.8 mm, 577 parts (0 on the bottom side), 321 nets.

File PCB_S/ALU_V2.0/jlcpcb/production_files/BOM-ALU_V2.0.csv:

Comment,Designator,Footprint,LCSC,Quantity
10kΩ,"R1,R10,R100,R101,R102,R103,R104,R105,R106,R107,R108,R109,R11,R110,R111,R112,R113,R114,R115,R116,R117,R118,R119,R12,R120,R121,R122,R123,R124,R125,R126,R127,R128,R129,R13,R130,R131,R132,R133,R134,R135,R136,R137,R138,R139,R14,R140,R141,R142,R143,R144,R145,R146,R147,R148,R149,R15,R150,R151,R152,R153,R154,R155,R156,R157,R158,R159,R16,R160,R161,R162,R163,R164,R165,R166,R167,R168,R169,R17,R170,R171,R172,R173,R174,R175,R176,R177,R178,R179,R18,R180,R181,R182,R183,R184,R185,R186,R187,R188,R189,R19,R190,R191,R192,R193,R194,R195,R196,R197,R198,R199,R2,R20,R200,R201,R202,R203,R204,R21,R22,R23,R24,R25,R26,R27,R28,R29,R3,R30,R31,R32,R33,R34,R35,R36,R37,R38,R39,R4,R40,R41,R42,R43,R44,R45,R46,R47,R48,R49,R5,R50,R51,R52,R53,R54,R55,R56,R57,R58,R59,R6,R60,R61,R62,R63,R64,R65,R66,R67,R68,R69,R7,R70,R71,R72,R73,R74,R75,R76,R77,R78,R79,R8,R80,R81,R82,R83,R84,R85,R86,R87,R88,R89,R9,R90,R91,R92,R93,R94,R95,R96,R97,R98,R99",R_0402,C25744,204
22uF,"C1,C2,C3,C4,C5,C6,C7,C8",C_0805,C45783,8
2N7002,"Q1,Q10,Q100,Q101,Q102,Q103,Q104,Q105,Q106,Q107,Q108,Q109,Q11,Q110,Q111,Q112,Q113,Q114,Q115,Q116,Q117,Q118,Q119,Q12,Q120,Q121,Q122,Q123,Q124,Q125,Q126,Q127,Q128,Q129,Q13,Q130,Q131,Q132,Q133,Q134,Q135,Q136,Q137,Q138,Q139,Q14,Q140,Q141,Q142,Q143,Q144,Q145,Q146,Q147,Q148,Q149,Q15,Q150,Q151,Q152,Q153,Q154,Q155,Q156,Q157,Q158,Q159,Q16,Q160,Q161,Q162,Q163,Q164,Q165,Q166,Q167,Q168,Q169,Q17,Q170,Q171,Q172,Q173,Q174,Q175,Q176,Q177,Q178,Q179,Q18,Q180,Q181,Q182,Q183,Q184,Q185,Q186,Q187,Q188,Q189,Q19,Q190,Q191,Q192,Q193,Q194,Q195,Q196,Q197,Q198,Q199,Q2,Q20,Q200,Q201,Q202,Q203,Q204,Q205,Q206,Q207,Q208,Q209,Q21,Q210,Q211,Q212,Q213,Q214,Q215,Q216,Q217,Q218,Q219,Q22,Q220,Q221,Q222,Q223,Q224,Q225,Q226,Q227,Q228,Q229,Q23,Q230,Q231,Q232,Q233,Q234,Q235,Q236,Q237,Q238,Q239,Q24,Q240,Q241,Q242,Q243,Q244,Q245,Q246,Q247,Q248,Q249,Q25,Q250,Q251,Q252,Q253,Q254,Q255,Q256,Q257,Q258,Q259,Q26,Q260,Q261,Q262,Q263,Q264,Q265,Q266,Q267,Q268,Q269,Q27,Q270,Q271,Q272,Q273,Q274,Q275,Q276,Q277,Q278,Q279,Q28,Q280,Q281,Q282,Q283,Q284,Q285,Q286,Q287,Q288,Q289,Q29,Q290,Q291,Q292,Q293,Q294,Q295,Q296,Q297,Q298,Q299,Q3,Q30,Q300,Q301,Q302,Q303,Q304,Q305,Q306,Q307,Q308,Q309,Q31,Q310,Q311,Q312,Q313,Q314,Q315,Q316,Q317,Q318,Q319,Q32,Q320,Q33,Q34,Q35,Q36,Q37,Q38,Q39,Q4,Q40,Q41,Q42,Q43,Q44,Q45,Q46,Q47,Q48,Q49,Q5,Q50,Q51,Q52,Q53,Q54,Q55,Q56,Q57,Q58,Q59,Q6,Q60,Q61,Q62,Q63,Q64,Q65,Q66,Q67,Q68,Q69,Q7,Q70,Q71,Q72,Q73,Q74,Q75,Q76,Q77,Q78,Q79,Q8,Q80,Q81,Q82,Q83,Q84,Q85,Q86,Q87,Q88,Q89,Q9,Q90,Q91,Q92,Q93,Q94,Q95,Q96,Q97,Q98,Q99",SOT-23,C8545,320
Red,"D1,D10,D11,D12,D13,D14,D15,D16,D17,D18,D19,D2,D20,D21,D22,D23,D24,D25,D26,D27,D28,D29,D3,D30,D31,D32,D33,D34,D35,D36,D4,D5,D6,D7,D8,D9",D_0603,C2286,36
Conn_02x08_Odd_Even,J2,PinSocket_2x08_P2.54mm_Vertical,,1
Conn_01x02_Pin,J6,PinHeader_1x02_P2.54mm_Vertical,,1
Conn_02x08_Odd_Even,J1,PinSocket_2x08_P2.54mm_Vertical,,1
Conn_01x02_Pin,J4,PinHeader_1x02_P2.54mm_Vertical,,1
Conn_02x08_Odd_Even,J3,PinSocket_2x08_P2.54mm_Vertical,,1

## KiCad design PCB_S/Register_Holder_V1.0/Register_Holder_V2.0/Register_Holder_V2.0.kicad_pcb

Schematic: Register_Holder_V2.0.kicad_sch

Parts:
C1, C2, C3, C4, C5, C6, C7, C8, C9, C10, C11, C12, C13, C14, C15, C16: 22uF; C_0805; Voltage Rated 25V; Tolerance ±20%; Part CL21A226MAQNNNE; LCSC C45783
D1, D2, D3, D4, D5, D6, D7, D8, D9, D10, D11, D12, D13, D14, D15, D16, D24: Red; D_0603; Part KT-0603R; LCSC C2286
H1, H2, H3, H4, H5, H6, H7, H8, H9, H10, H11, H12, H13, H14, H15, H16: MountingHole; MountingHole_2.2mm_M2
H17, H18, H19, H20: MountingHole; MountingHole_3.2mm_M3
J1, J2, J3, J4: Conn_01x21_Socket; PinHeader_1x21_P2.54mm_Vertical
J5, J7, J9, J12: Conn_02x08_Odd_Even; PinSocket_2x08_P2.54mm_Vertical
J13, J14, J15: Conn_01x02_Pin; PinHeader_1x02_P2.54mm_Vertical
Q1, Q2, Q3, Q4, Q5, Q6, Q7, Q8, Q9, Q10, Q11, Q12, Q13, Q14, Q15, Q16, Q17, Q18, Q19, Q20, Q21, Q22, Q23, Q24, Q25, Q26, Q27, Q28, Q29, Q30, Q31, Q32, Q33, Q34, Q35, Q36, Q37, Q38, Q39, Q40, Q41, Q42, Q43, Q44, Q45, Q46, Q47, Q48, Q49, Q50, Q51, Q52, Q53, Q54, Q55, Q56, Q57, Q58, Q59, Q60, Q61, Q62, Q63, Q64, Q65, Q66, Q67, Q68, Q69, Q70, Q71, Q72, Q73, Q74, Q75, Q76, Q77, Q78, Q79, Q80, Q81, Q82, Q83, Q84, Q85, Q86, Q87, Q88, Q89, Q90, Q91, Q92, Q93, Q94, Q95, Q96, Q97, Q98, Q99, Q100, Q101, Q102, Q103, Q104, Q105, Q106, Q107, Q108, Q109, Q110, Q111, Q112, Q113, Q114, Q115, Q116, Q117, Q118, Q119, Q120, Q121, Q122, Q123, Q124, Q125, Q126, Q127, Q128, Q129, Q130, Q131, Q132, Q133, Q134, Q135, Q136, Q137, Q138, Q139, Q140, Q141, Q142, Q143, Q144, Q145, Q146, Q147, Q148, Q149, Q150, Q151, Q152, Q153, Q154, Q155, Q156, Q157, Q158, Q159, Q160, Q161, Q162, Q163, Q164, Q165, Q166, Q167, Q168: 2N7002; SOT-23
R1, R2, R3, R4, R5, R6, R7, R8, R9, R10, R11, R12, R13, R14, R15, R16, R17, R18, R19, R20, R21, R22, R23, R24, R25, R26, R27, R28, R29, R30, R31, R32, R33, R34, R35, R36, R37, R38, R39, R40, R41, R42, R43, R44, R45, R46, R47, R48, R49, R50, R51, R52, R53, R54, R55, R56, R57, R58, R59, R60, R61, R62, R63, R64, R65, R66: 10kΩ; R_0402; Overload Voltage (Max) 50V; Tolerance ±1%; Part 0402WGF1002TCE; LCSC C25744

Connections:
/ALU B -> FF: J5.7, Q161.1 (G), Q162.1 (G), Q163.1 (G), Q164.1 (G), Q165.1 (G), Q166.1 (G), Q167.1 (G), Q168.1 (G)
GND: C1.2, C2.2, C3.2, C4.2, C5.2, C6.2, C7.2, C8.2, C9.2, C10.2, C11.2, C12.2, C13.2, C14.2, C15.2, C16.2, D8.1, J1.2, J2.2, J3.2, J4.2, J5.1, J9.3, J9.7, J9.11, J9.15, J12.1, J12.5, J12.9, J12.13, J13.2, J14.2, J15.2, Q2.2 (S), Q4.2 (S), Q6.2 (S), Q8.2 (S), Q10.2 (S), Q12.2 (S), Q14.2 (S), Q16.2 (S), Q17.2 (S), Q18.2 (S), Q19.2 (S), Q20.2 (S), Q21.2 (S), Q22.2 (S), Q23.2 (S), Q24.2 (S), Q33.2 (S), Q34.2 (S), Q35.2 (S), Q36.2 (S), Q37.2 (S), Q38.2 (S), Q39.2 (S), Q40.2 (S), Q49.2 (S), Q50.2 (S), Q51.2 (S), Q52.2 (S), Q53.2 (S), Q54.2 (S), Q55.2 (S), Q56.2 (S), Q65.2 (S), Q66.2 (S), Q67.2 (S), Q68.2 (S), Q69.2 (S), Q70.2 (S), Q71.2 (S), Q72.2 (S), Q81.2 (S), Q82.2 (S), Q83.2 (S), Q84.2 (S), Q85.2 (S), Q86.2 (S), Q87.2 (S), Q88.2 (S), Q97.2 (S), Q98.2 (S), Q99.2 (S), Q100.2 (S), Q101.2 (S), Q102.2 (S), Q103.2 (S), Q104.2 (S), Q113.2 (S), Q114.2 (S), Q115.2 (S), Q116.2 (S), Q117.2 (S), Q118.2 (S), Q119.2 (S), Q120.2 (S), Q129.2 (S), Q130.2 (S), Q131.2 (S), Q132.2 (S), Q133.2 (S), Q134.2 (S), Q135.2 (S), Q136.2 (S), Q137.2 (S), Q138.2 (S), Q139.2 (S), Q140.2 (S), Q141.2 (S), Q142.2 (S), Q143.2 (S), Q144.2 (S), Q145.2 (S), Q146.2 (S), Q147.2 (S), Q148.2 (S), Q149.2 (S), Q150.2 (S), Q151.2 (S), Q152.2 (S), Q153.2 (S), Q154.2 (S), Q155.2 (S), Q156.2 (S), Q157.2 (S), Q158.2 (S), Q159.2 (S), Q160.2 (S), Q161.2 (S), Q162.2 (S), Q163.2 (S), Q164.2 (S), Q165.2 (S), Q166.2 (S), Q167.2 (S), Q168.2 (S)
unnamed: D1.2, R53.2, R54.2
unnamed: D2.2, R55.2, R56.2
unnamed: D3.2, R57.2, R58.2
unnamed: D4.2, R59.2, R60.2
unnamed: D5.2, R61.2, R62.2
unnamed: D6.2, R63.2, R64.2
unnamed: D7.2, R65.2, R66.2
unnamed: D8.2, R33.2, R34.2
unnamed: D9.2, R37.2, R38.2
unnamed: D10.2, R35.2, R36.2
unnamed: D11.2, R39.2, R40.2
unnamed: D12.2, R41.2, R42.2
unnamed: D13.2, R43.2, R44.2
unnamed: D14.2, R45.2, R46.2
unnamed: D15.2, R47.2, R48.2
unnamed: D16.2, R49.2, R50.2
unnamed: D24.2, R51.2, R52.2
unnamed: J1.4, J5.15
unnamed: J1.6, J2.6, J3.6, J4.6, J9.2, J12.16, Q160.1 (G)
unnamed: J1.7, J2.7, J3.7, J4.7, J9.4, J12.14, Q159.1 (G)
unnamed: J1.8, J2.8, J3.8, J4.8, J9.6, J12.12, Q158.1 (G)
unnamed: J1.9, J2.9, J3.9, J4.9, J9.8, J12.10, Q157.1 (G)
unnamed: J1.10, J2.10, J3.10, J4.10, J9.10, J12.8, Q156.1 (G)
unnamed: J1.11, J2.11, J3.11, J4.11, J9.12, J12.6, Q155.1 (G)
unnamed: J1.12, J2.12, J3.12, J4.12, J9.14, J12.4, Q153.1 (G)
unnamed: J1.13, J2.13, J3.13, J4.13, J9.16, J12.2, Q154.1 (G)
unnamed: J1.14, Q15.1 (G), Q80.1 (G)
unnamed: J1.15, Q13.1 (G), Q79.1 (G)
unnamed: J1.16, Q11.1 (G), Q78.1 (G)
unnamed: J1.17, Q9.1 (G), Q77.1 (G)
unnamed: J1.18, Q7.1 (G), Q76.1 (G)
unnamed: J1.19, Q5.1 (G), Q75.1 (G)
unnamed: J1.20, Q3.1 (G), Q74.1 (G)
unnamed: J1.21, Q1.1 (G), Q73.1 (G)
unnamed: J2.4, J5.13
unnamed: J2.14, Q32.1 (G), Q48.1 (G)
unnamed: J2.15, Q31.1 (G), Q47.1 (G)
unnamed: J2.16, Q30.1 (G), Q46.1 (G)
unnamed: J2.17, Q29.1 (G), Q45.1 (G)
unnamed: J2.18, Q28.1 (G), Q44.1 (G)
unnamed: J2.19, Q27.1 (G), Q43.1 (G)
unnamed: J2.20, Q26.1 (G), Q42.1 (G)
unnamed: J2.21, Q25.1 (G), Q41.1 (G)
unnamed: J3.4, J5.11
unnamed: J3.14, Q64.1 (G), Q96.1 (G)
unnamed: J3.15, Q63.1 (G), Q95.1 (G)
unnamed: J3.16, Q62.1 (G), Q94.1 (G)
unnamed: J3.17, Q61.1 (G), Q93.1 (G)
unnamed: J3.18, Q60.1 (G), Q92.1 (G)
unnamed: J3.19, Q59.1 (G), Q91.1 (G)
unnamed: J3.20, Q58.1 (G), Q90.1 (G)
unnamed: J3.21, Q57.1 (G), Q89.1 (G)
unnamed: J4.4, J5.9
unnamed: J4.14, Q112.1 (G), Q128.1 (G)
unnamed: J4.15, Q111.1 (G), Q127.1 (G)
unnamed: J4.16, Q110.1 (G), Q126.1 (G)
unnamed: J4.17, Q109.1 (G), Q125.1 (G)
unnamed: J4.18, Q108.1 (G), Q124.1 (G)
unnamed: J4.19, Q107.1 (G), Q123.1 (G)
unnamed: J4.20, Q106.1 (G), Q122.1 (G)
unnamed: J4.21, Q105.1 (G), Q121.1 (G)
unnamed: J5.2, Q113.1 (G), Q114.1 (G), Q115.1 (G), Q116.1 (G), Q117.1 (G), Q118.1 (G), Q119.1 (G), Q120.1 (G), Q152.1 (G)
unnamed: J5.4, Q81.1 (G), Q82.1 (G), Q83.1 (G), Q84.1 (G), Q85.1 (G), Q86.1 (G), Q87.1 (G), Q88.1 (G), Q150.1 (G)
unnamed: J5.6, Q33.1 (G), Q34.1 (G), Q35.1 (G), Q36.1 (G), Q37.1 (G), Q38.1 (G), Q39.1 (G), Q40.1 (G), Q148.1 (G)
unnamed: J5.8, Q65.1 (G), Q66.1 (G), Q67.1 (G), Q68.1 (G), Q69.1 (G), Q70.1 (G), Q71.1 (G), Q72.1 (G), Q146.1 (G)
unnamed: J5.10, Q97.1 (G), Q98.1 (G), Q99.1 (G), Q100.1 (G), Q101.1 (G), Q102.1 (G), Q103.1 (G), Q104.1 (G), Q151.1 (G)
unnamed: J5.12, Q49.1 (G), Q50.1 (G), Q51.1 (G), Q52.1 (G), Q53.1 (G), Q54.1 (G), Q55.1 (G), Q56.1 (G), Q149.1 (G)
unnamed: J5.14, Q17.1 (G), Q18.1 (G), Q19.1 (G), Q20.1 (G), Q21.1 (G), Q22.1 (G), Q23.1 (G), Q24.1 (G), Q147.1 (G)
unnamed: J5.16, Q2.1 (G), Q4.1 (G), Q6.1 (G), Q8.1 (G), Q10.1 (G), Q12.1 (G), Q14.1 (G), Q16.1 (G), Q145.1 (G)
unnamed: J7.1, Q137.3 (D), R25.2
unnamed: J7.2, Q129.3 (D), R1.2
unnamed: J7.3, Q138.3 (D), R26.2
unnamed: J7.4, Q130.3 (D), R2.2
unnamed: J7.5, Q139.3 (D), R27.2
unnamed: J7.6, Q131.3 (D), R3.2
unnamed: J7.7, Q140.3 (D), R28.2
unnamed: J7.8, Q132.3 (D), R4.2
unnamed: J7.9, Q141.3 (D), R29.2
unnamed: J7.10, Q133.3 (D), R5.2
unnamed: J7.11, Q142.3 (D), R30.2
unnamed: J7.12, Q134.3 (D), R6.2
unnamed: J7.13, Q143.3 (D), R31.2
unnamed: J7.14, Q135.3 (D), R7.2
unnamed: J7.15, Q144.3 (D), R32.2
unnamed: J7.16, Q136.3 (D), R8.2
unnamed: Q1.3 (D), Q25.3 (D), Q57.3 (D), Q105.3 (D), Q136.1 (G), R16.2
unnamed: Q1.2 (S), Q2.3 (D)
unnamed: Q3.2 (S), Q4.3 (D)
unnamed: Q5.2 (S), Q6.3 (D)
unnamed: Q7.2 (S), Q8.3 (D)
unnamed: Q9.2 (S), Q10.3 (D)
unnamed: Q11.3 (D), Q30.3 (D), Q62.3 (D), Q110.3 (D), Q131.1 (G), R11.2
unnamed: Q11.2 (S), Q12.3 (D)
unnamed: Q13.2 (S), Q14.3 (D)
unnamed: Q15.2 (S), Q16.3 (D)
unnamed: Q17.3 (D), Q25.2 (S)
unnamed: Q18.3 (D), Q26.2 (S)
unnamed: Q19.3 (D), Q27.2 (S)
unnamed: Q20.3 (D), Q28.2 (S)
unnamed: Q21.3 (D), Q29.2 (S)
unnamed: Q22.3 (D), Q30.2 (S)
unnamed: Q23.3 (D), Q31.2 (S)
unnamed: Q24.3 (D), Q32.2 (S)
unnamed: Q33.3 (D), Q41.2 (S)
unnamed: Q34.3 (D), Q42.2 (S)
unnamed: Q35.3 (D), Q43.2 (S)
unnamed: Q36.3 (D), Q44.2 (S)
unnamed: Q37.3 (D), Q45.2 (S)
unnamed: Q38.3 (D), Q46.2 (S)
unnamed: Q39.3 (D), Q47.2 (S)
unnamed: Q40.3 (D), Q48.2 (S)
unnamed: Q49.3 (D), Q57.2 (S)
unnamed: Q50.3 (D), Q58.2 (S)
unnamed: Q51.3 (D), Q59.2 (S)
unnamed: Q52.3 (D), Q60.2 (S)
unnamed: Q53.3 (D), Q61.2 (S)
unnamed: Q54.3 (D), Q62.2 (S)
unnamed: Q55.3 (D), Q63.2 (S)
unnamed: Q56.3 (D), Q64.2 (S)
unnamed: Q65.3 (D), Q73.2 (S)
unnamed: Q66.3 (D), Q74.2 (S)
unnamed: Q67.3 (D), Q75.2 (S)
unnamed: Q68.3 (D), Q76.2 (S)
unnamed: Q69.3 (D), Q77.2 (S)
unnamed: Q70.3 (D), Q78.2 (S)
unnamed: Q71.3 (D), Q79.2 (S)
unnamed: Q72.3 (D), Q80.2 (S)
unnamed: Q81.3 (D), Q89.2 (S)
unnamed: Q82.3 (D), Q90.2 (S)
unnamed: Q83.3 (D), Q91.2 (S)
unnamed: Q84.3 (D), Q92.2 (S)
unnamed: Q85.3 (D), Q93.2 (S)
unnamed: Q86.3 (D), Q94.2 (S)
unnamed: Q87.3 (D), Q95.2 (S)
unnamed: Q88.3 (D), Q96.2 (S)
unnamed: Q100.3 (D), Q108.2 (S)
unnamed: Q101.3 (D), Q109.2 (S)
unnamed: Q102.3 (D), Q110.2 (S)
unnamed: Q103.3 (D), Q111.2 (S)
unnamed: Q104.3 (D), Q112.2 (S)
unnamed: Q97.3 (D), Q105.2 (S)
unnamed: Q3.3 (D), Q26.3 (D), Q58.3 (D), Q106.3 (D), Q135.1 (G), R15.2
unnamed: Q98.3 (D), Q106.2 (S)
unnamed: Q5.3 (D), Q27.3 (D), Q59.3 (D), Q107.3 (D), Q134.1 (G), R14.2
unnamed: Q99.3 (D), Q107.2 (S)
unnamed: Q7.3 (D), Q28.3 (D), Q60.3 (D), Q108.3 (D), Q133.1 (G), R13.2
unnamed: Q9.3 (D), Q29.3 (D), Q61.3 (D), Q109.3 (D), Q132.1 (G), R12.2
unnamed: Q13.3 (D), Q31.3 (D), Q63.3 (D), Q111.3 (D), Q130.1 (G), R10.2
unnamed: Q15.3 (D), Q32.3 (D), Q64.3 (D), Q112.3 (D), Q129.1 (G), R9.2
unnamed: Q113.3 (D), Q121.2 (S)
unnamed: Q114.3 (D), Q122.2 (S)
unnamed: Q115.3 (D), Q123.2 (S)
unnamed: Q116.3 (D), Q124.2 (S)
unnamed: Q117.3 (D), Q125.2 (S)
unnamed: Q118.3 (D), Q126.2 (S)
unnamed: Q119.3 (D), Q127.2 (S)
unnamed: Q120.3 (D), Q128.2 (S)
unnamed: Q41.3 (D), Q73.3 (D), Q89.3 (D), Q121.3 (D), Q144.1 (G), Q168.3 (D), R24.2
unnamed: Q42.3 (D), Q74.3 (D), Q90.3 (D), Q122.3 (D), Q143.1 (G), Q167.3 (D), R23.2
unnamed: Q43.3 (D), Q75.3 (D), Q91.3 (D), Q123.3 (D), Q142.1 (G), Q166.3 (D), R22.2
unnamed: Q44.3 (D), Q76.3 (D), Q92.3 (D), Q124.3 (D), Q141.1 (G), Q165.3 (D), R21.2
unnamed: Q45.3 (D), Q77.3 (D), Q93.3 (D), Q125.3 (D), Q140.1 (G), Q164.3 (D), R20.2
unnamed: Q46.3 (D), Q78.3 (D), Q94.3 (D), Q126.3 (D), Q139.1 (G), Q163.3 (D), R19.2
unnamed: Q47.3 (D), Q79.3 (D), Q95.3 (D), Q127.3 (D), Q138.1 (G), Q162.3 (D), R18.2
unnamed: Q48.3 (D), Q80.3 (D), Q96.3 (D), Q128.3 (D), Q137.1 (G), Q161.3 (D), R17.2
unnamed: D24.1, Q145.3 (D)
unnamed: D1.1, Q146.3 (D)
unnamed: D2.1, Q147.3 (D)
unnamed: D3.1, Q148.3 (D)
unnamed: D4.1, Q149.3 (D)
unnamed: D5.1, Q150.3 (D)
unnamed: D6.1, Q151.3 (D)
unnamed: D7.1, Q152.3 (D)
unnamed: D9.1, Q153.3 (D)
unnamed: D10.1, Q154.3 (D)
unnamed: D11.1, Q155.3 (D)
unnamed: D12.1, Q156.3 (D)
unnamed: D13.1, Q157.3 (D)
unnamed: D14.1, Q158.3 (D)
unnamed: D15.1, Q159.3 (D)
unnamed: D16.1, Q160.3 (D)
RST: J1.3, J2.3, J3.3, J4.3, J5.3
Rising_Edge: J1.5, J2.5, J3.5, J4.5, J5.5
VCC: C1.1, C2.1, C3.1, C4.1, C5.1, C6.1, C7.1, C8.1, C9.1, C10.1, C11.1, C12.1, C13.1, C14.1, C15.1, C16.1, J1.1, J2.1, J3.1, J4.1, J9.1, J9.5, J9.9, J9.13, J12.3, J12.7, J12.11, J12.15, J13.1, J14.1, J15.1, R1.1, R2.1, R3.1, R4.1, R5.1, R6.1, R7.1, R8.1, R9.1, R10.1, R11.1, R12.1, R13.1, R14.1, R15.1, R16.1, R17.1, R18.1, R19.1, R20.1, R21.1, R22.1, R23.1, R24.1, R25.1, R26.1, R27.1, R28.1, R29.1, R30.1, R31.1, R32.1, R33.1, R34.1, R35.1, R36.1, R37.1, R38.1, R39.1, R40.1, R41.1, R42.1, R43.1, R44.1, R45.1, R46.1, R47.1, R48.1, R49.1, R50.1, R51.1, R52.1, R53.1, R54.1, R55.1, R56.1, R57.1, R58.1, R59.1, R60.1, R61.1, R62.1, R63.1, R64.1, R65.1, R66.1

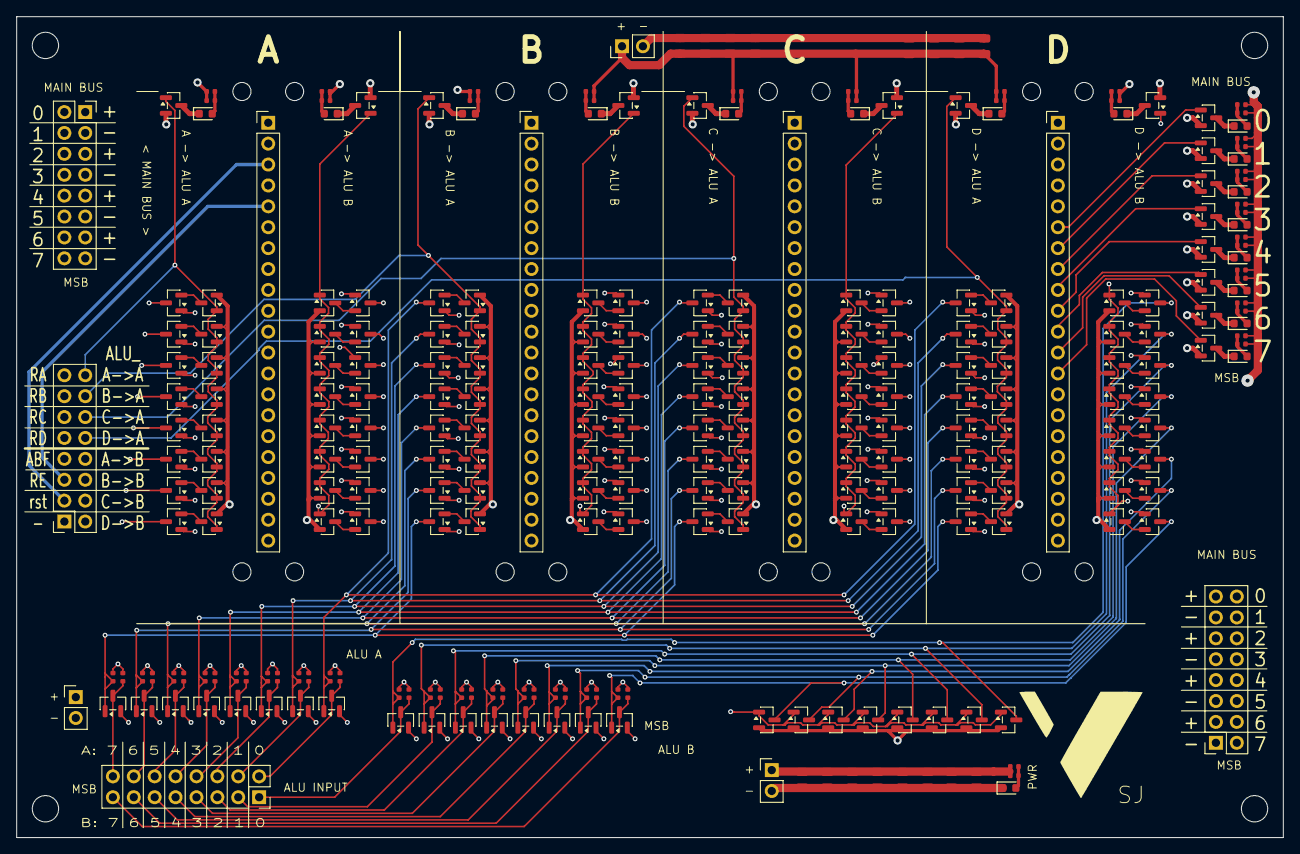
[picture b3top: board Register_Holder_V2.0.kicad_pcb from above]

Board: 6 copper layers, 154.0 x 99.8 mm, 298 parts (0 on the bottom side), 186 nets.
